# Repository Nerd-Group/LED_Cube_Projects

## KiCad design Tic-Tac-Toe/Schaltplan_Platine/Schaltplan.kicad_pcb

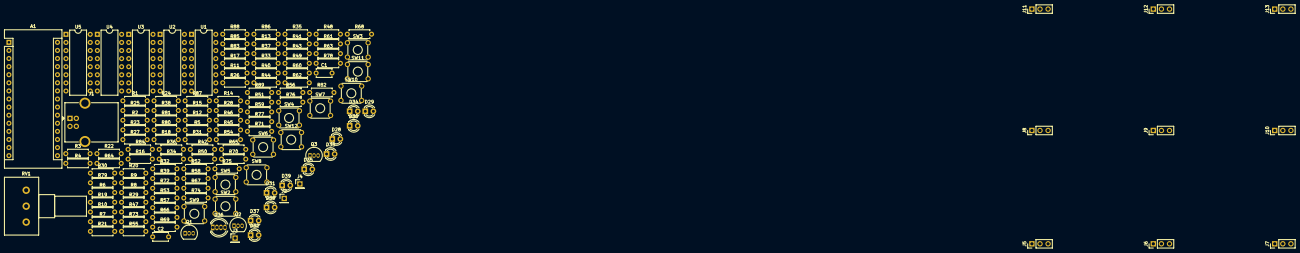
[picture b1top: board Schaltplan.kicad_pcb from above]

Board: 2 copper layers, 137 parts (0 on the bottom side), 146 nets, no tracks yet.

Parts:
A1: Arduino_Nano_v3.x; Arduino_Nano
C1, C2: 100n; C_Disc_D4.7mm_W2.5mm_P5.00mm
D28, D29, D30, D31, D32, D33, D34, D35, D37, D38, D39: LED; LED_D3.0mm
D36: LED_CRGB; LED_D5.0mm-4_RGB
J1: USB_B; USB_B_OST_USB-B1HSxx_Horizontal
J2, J3, J4: Conn_01x01_Male; PinHeader_1x01_P2.54mm_Vertical
J5, J6, J7, J8, J9, J10, J11, J12, J13: Conn_01x03_Male; PinHeader_1x03_P2.54mm_Vertical
Q1, Q2, Q3: BC337; TO-92_Inline
R1, R2, R3, R8, R45, R46, R50, R65, R73, R74, R78, R79, R83, R84, R88, R89: 10K; R_Axial_DIN0207_L6.3mm_D2.5mm_P7.62mm_Horizontal
R4, R5, R6, R38, R42, R43, R44, R51, R52, R64, R66, R70, R71, R72, R75, R76, R77, R80, R81, R82, R85, R86, R87: 1K; R_Axial_DIN0207_L6.3mm_D2.5mm_P7.62mm_Horizontal
R7, R9, R10, R11, R12, R13, R14, R15, R16, R17, R18, R19, R20, R21, R22, R23, R24, R25, R26, R27, R28, R29, R30, R31, R32, R33, R34, R35, R36, R37, R39, R40, R41, R47, R48, R49, R53, R54, R55, R56, R57, R58, R59, R60, R61, R62, R63, R67, R68, R69: 220; R_Axial_DIN0207_L6.3mm_D2.5mm_P7.62mm_Horizontal
RV1: 2K-22K; Potentiometer_Alps_RK163_Single_Horizontal
SW2, SW3, SW4, SW5, SW6, SW7, SW8, SW9, SW10, SW11, SW12: SW_Push_Dual; SW_TH_Tactile_Omron_B3F-10xx
U1, U2, U3, U4, U5: 74HC595; DIP-16_W7.62mm

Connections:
+5V: A1.27, C1.1, J1.1, R7.2, R8.1, R45.2, R47.2, R50.2, R58.2, R65.1, R73.2, R78.2, R83.2, R88.2, RV1.1, U1.16, U2.16, U3.16, U4.16, U5.16
GND: A1.4, A1.29, C1.2, D28.1, D29.1, D30.1, D31.1, D32.1, D33.1, D34.1, D35.1, D36.1, D37.1, D38.1, D39.1, J1.4, Q1.3, Q2.3, Q3.3, R1.1, R2.1, R3.1, R38.1, R46.2, R51.2, R52.1, R64.1, R66.1, R74.2, R79.2, R84.2, R89.2, RV1.3, U1.8, U2.8, U3.8, U4.8, U5.8
unnamed: A1.5, R51.1, SW8.1, SW8.3
unnamed: A1.6, R42.1
unnamed: A1.7, R44.2
unnamed: A1.8, R43.2
unnamed: A1.9, R72.2, R77.2, R82.2, R87.2
unnamed: A1.10, R71.2, R76.2, R81.2, R86.2
unnamed: A1.11, R70.1
unnamed: A1.12, Q3.2, R3.2, R6.2
unnamed: A1.13, Q2.2, R2.2, R5.2
unnamed: A1.14, Q1.2, R1.2, R4.2
unnamed: A1.15, R56.2
unnamed: A1.16, R57.2
unnamed: A1.18, R8.2
unnamed: A1.19, R61.2
unnamed: A1.20, R62.2
unnamed: A1.21, R63.2
unnamed: A1.22, R69.2
unnamed: A1.23, RV1.2
unnamed: A1.24, R38.2, SW2.1, SW2.3, SW3.1, SW3.3, SW4.1, SW4.3
unnamed: A1.25, R52.2, SW5.1, SW5.3, SW6.1, SW6.3, SW7.1, SW7.3
unnamed: A1.26, R66.2, SW10.1, SW10.3, SW11.1, SW11.3, SW12.1, SW12.3
unnamed: A1.3, A1.28, SW9.2
unnamed: C2.1, R64.2, SW9.1, SW9.3
unnamed: C2.2, R65.2, SW9.4
unnamed: D28.2, R39.1
unnamed: D29.2, R40.1
unnamed: D30.2, R41.1
unnamed: D31.2, R53.1
unnamed: D32.2, R54.1
unnamed: D33.2, R55.1
unnamed: D34.2, R56.1
unnamed: D35.2, R57.1
unnamed: D36.2, R61.1
unnamed: D36.3, R62.1
unnamed: D36.4, R63.1
unnamed: D37.2, R67.1
unnamed: D38.2, R68.1
unnamed: D39.2, R69.1
unnamed: J2.1, Q1.1
unnamed: J3.1, Q2.1
unnamed: J4.1, Q3.1
unnamed: J5.1, R11.2
unnamed: J5.2, R10.2
unnamed: J5.3, R9.2
unnamed: J6.1, R14.2
unnamed: J6.2, R13.2
unnamed: J6.3, R12.2
unnamed: J7.1, R17.2
unnamed: J7.2, R16.2
unnamed: J7.3, R15.2
unnamed: J8.1, R20.2
unnamed: J8.2, R19.2
unnamed: J8.3, R18.2
unnamed: J9.1, R23.2
unnamed: J9.2, R22.2
unnamed: J9.3, R21.2
unnamed: J10.1, R26.2
unnamed: J10.2, R25.2
unnamed: J10.3, R24.2
unnamed: J11.1, R29.2
unnamed: J11.2, R28.2
unnamed: J11.3, R27.2
unnamed: J12.1, R32.2
unnamed: J12.2, R31.2
unnamed: J12.3, R30.2
unnamed: J13.1, R35.2
unnamed: J13.2, R34.2
unnamed: J13.3, R33.2
unnamed: R4.1, U2.2
unnamed: R5.1, U2.1
unnamed: R6.1, U2.15
unnamed: R9.1, U2.3
unnamed: R10.1, U2.4
unnamed: R11.1, U2.5
unnamed: R12.1, U2.6
unnamed: R13.1, U2.7
unnamed: R14.1, U3.15
unnamed: R15.1, U3.1
unnamed: R16.1, U3.2
unnamed: R17.1, U3.3
unnamed: R18.1, U3.4
unnamed: R19.1, U3.5
unnamed: R20.1, U3.6
unnamed: R21.1, U3.7
unnamed: R22.1, U4.15
unnamed: R23.1, U4.1
unnamed: R24.1, U4.2
unnamed: R25.1, U4.3
unnamed: R26.1, U4.4
unnamed: R27.1, U4.5
unnamed: R28.1, U4.6
unnamed: R29.1, U4.7
unnamed: R30.1, U5.15
unnamed: R31.1, U5.1
unnamed: R32.1, U5.2
unnamed: R33.1, U5.3
unnamed: R34.1, U5.4
unnamed: R35.1, U5.5
unnamed: R36.1, R37.2, SW3.2, SW3.4
unnamed: R7.1, R36.2, SW2.2, SW2.4
unnamed: R37.1, SW4.2, SW4.4
unnamed: R39.2, U1.15
unnamed: R40.2, U1.1
unnamed: R41.2, U1.2
unnamed: R42.2, U1.14
unnamed: R43.1, U1.11
unnamed: R44.1, U1.10
unnamed: R45.1, U1.12
unnamed: R46.1, U1.13
unnamed: R47.1, R48.2, SW5.2, SW5.4
unnamed: R48.1, R49.2, SW6.2, SW6.4
unnamed: R49.1, SW7.2, SW7.4
unnamed: R50.1, SW8.2, SW8.4
unnamed: R53.2, U1.3
unnamed: R54.2, U1.4
unnamed: R55.2, U1.5
unnamed: R58.1, R59.2, SW10.2, SW10.4
unnamed: R59.1, R60.2, SW11.2, SW11.4
unnamed: R60.1, SW12.2, SW12.4
unnamed: R67.2, U1.6
unnamed: R68.2, U1.7
unnamed: R70.2, U2.14
unnamed: R71.1, U2.11
unnamed: R72.1, U2.10
unnamed: R73.1, U2.12
unnamed: R74.1, U2.13
unnamed: R75.1, U2.9
unnamed: R75.2, U3.14
unnamed: R76.1, U3.11
unnamed: R77.1, U3.10
unnamed: R78.1, U3.12
unnamed: R79.1, U3.13
unnamed: R80.1, U3.9
unnamed: R80.2, U4.14
unnamed: R81.1, U4.11
unnamed: R82.1, U4.10
unnamed: R83.1, U4.12
unnamed: R84.1, U4.13
unnamed: R85.1, U4.9
unnamed: R85.2, U5.14
unnamed: R86.1, U5.11
unnamed: R87.1, U5.10
unnamed: R88.1, U5.12
unnamed: R89.1, U5.13

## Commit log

2018-11-02 Snake Projekt integriert
2018-11-02 Blinkendes Thingiverse Projekt integriert
2018-11-07 Schaltplan fertig erstellt
2018-11-17 Footprints zum Tic-Tac-Toe zugeordnet
2018-12-07 Started a new Project
2019-01-14 Schaltplan Update
2019-12-28 Merged two repos
2020-04-04 start reogrnanizing
2020-04-20 Random: Update the firmware for an 8x8x8 Cube
